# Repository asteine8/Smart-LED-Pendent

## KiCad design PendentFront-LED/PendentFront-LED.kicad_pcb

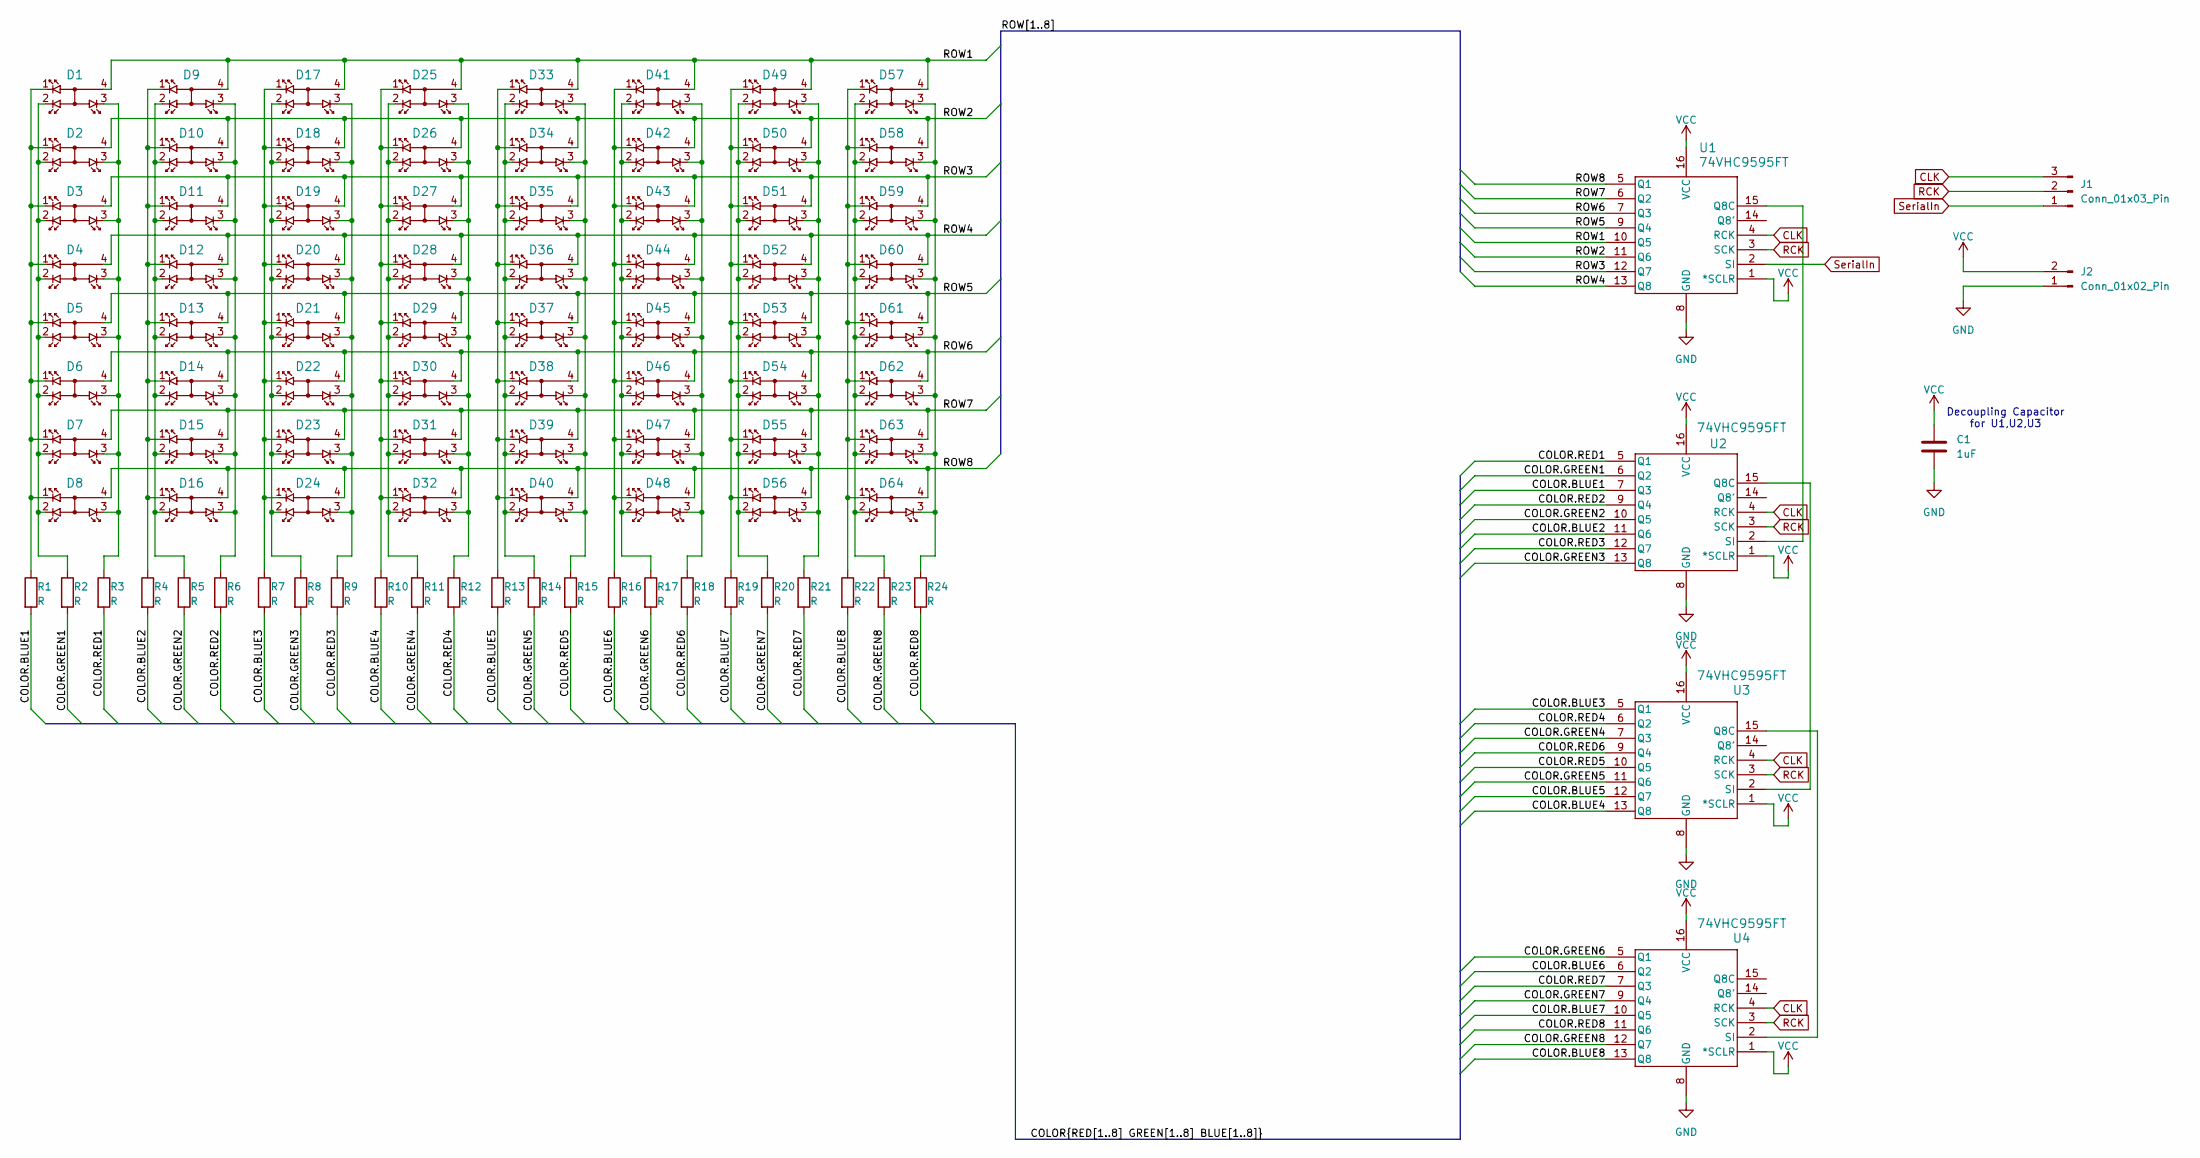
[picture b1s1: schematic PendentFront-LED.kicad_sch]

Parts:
C1: 1uF; C_0402_1005Metric_Pad0.74x0.62mm_HandSolder
D1, D2, D3, D4, D5, D6, D7, D8, D9, D10, D11, D12, D13, D14, D15, D16, D17, D18, D19, D20, D21, D22, D23, D24, D25, D26, D27, D28, D29, D30, D31, D32, D33, D34, D35, D36, D37, D38, D39, D40, D41, D42, D43, D44, D45, D46, D47, D48, D49, D50, D51, D52, D53, D54, D55, D56, D57, D58, D59, D60, D61, D62, D63, D64: UHD111A-FKA-C3K23E1L3VG5ZB3Z3; SMD4_UHD111A-FKA_CRW
J1: Conn_01x03_Pin; PinHeader_1x03_P1.27mm_Vertical
J2: Conn_01x02_Pin; PinHeader_1x02_P1.27mm_Vertical
R1, R2, R3, R4, R5, R6, R7, R8, R9, R10, R11, R12, R13, R14, R15, R16, R17, R18, R19, R20, R21, R22, R23, R24: R; R_0402_1005Metric
U1, U2, U3, U4: 74VHC9595FT; TSSOP16B_TOS

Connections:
/COLOR.BLUE1: R1.2, U2.7 (Q3)
/COLOR.BLUE2: R4.2, U2.11 (Q6)
/COLOR.BLUE3: R7.2, U3.5 (Q1)
/COLOR.BLUE4: R10.2, U3.13 (Q8)
/COLOR.BLUE5: R13.2, U3.12 (Q7)
/COLOR.BLUE6: R16.2, U4.6 (Q2)
/COLOR.BLUE7: R19.2, U4.10 (Q5)
/COLOR.BLUE8: R22.2, U4.13 (Q8)
/COLOR.GREEN1: R2.2, U2.6 (Q2)
/COLOR.GREEN2: R5.2, U2.10 (Q5)
/COLOR.GREEN3: R8.2, U2.13 (Q8)
/COLOR.GREEN4: R11.2, U3.7 (Q3)
/COLOR.GREEN5: R14.2, U3.11 (Q6)
/COLOR.GREEN6: R17.2, U4.5 (Q1)
/COLOR.GREEN7: R20.2, U4.9 (Q4)
/COLOR.GREEN8: R23.2, U4.12 (Q7)
/COLOR.RED1: R3.2, U2.5 (Q1)
/COLOR.RED2: R6.2, U2.9 (Q4)
/COLOR.RED3: R9.2, U2.12 (Q7)
/COLOR.RED4: R12.2, U3.6 (Q2)
/COLOR.RED5: R15.2, U3.10 (Q5)
/COLOR.RED6: R18.2, U3.9 (Q4)
/COLOR.RED7: R21.2, U4.7 (Q3)
/COLOR.RED8: R24.2, U4.11 (Q6)
/ROW1: D1.4, D9.4, D17.4, D25.4, D33.4, D41.4, D49.4, D57.4, U1.10 (Q5)
/ROW2: D2.4, D10.4, D18.4, D26.4, D34.4, D42.4, D50.4, D58.4, U1.11 (Q6)
/ROW3: D3.4, D11.4, D19.4, D27.4, D35.4, D43.4, D51.4, D59.4, U1.12 (Q7)
/ROW4: D4.4, D12.4, D20.4, D28.4, D36.4, D44.4, D52.4, D60.4, U1.13 (Q8)
/ROW5: D5.4, D13.4, D21.4, D29.4, D37.4, D45.4, D53.4, D61.4, U1.9 (Q4)
/ROW6: D6.4, D14.4, D22.4, D30.4, D38.4, D46.4, D54.4, D62.4, U1.7 (Q3)
/ROW7: D7.4, D15.4, D23.4, D31.4, D39.4, D47.4, D55.4, D63.4, U1.6 (Q2)
/ROW8: D8.4, D16.4, D24.4, D32.4, D40.4, D48.4, D56.4, D64.4, U1.5 (Q1)
CLK: J1.3, U1.4 (RCK), U2.4 (RCK), U3.4 (RCK), U4.4 (RCK)
GND: C1.2, J2.1, U1.8 (GND), U2.8 (GND), U3.8 (GND), U4.8 (GND)
unnamed: D1.1, D2.1, D3.1, D4.1, D5.1, D6.1, D7.1, D8.1, R1.1
unnamed: D1.2, D2.2, D3.2, D4.2, D5.2, D6.2, D7.2, D8.2, R2.1
unnamed: D1.3, D2.3, D3.3, D4.3, D5.3, D6.3, D7.3, D8.3, R3.1
unnamed: D9.1, D10.1, D11.1, D12.1, D13.1, D14.1, D15.1, D16.1, R4.1
unnamed: D9.2, D10.2, D11.2, D12.2, D13.2, D14.2, D15.2, D16.2, R5.1
unnamed: D9.3, D10.3, D11.3, D12.3, D13.3, D14.3, D15.3, D16.3, R6.1
unnamed: D17.1, D18.1, D19.1, D20.1, D21.1, D22.1, D23.1, D24.1, R7.1
unnamed: D17.2, D18.2, D19.2, D20.2, D21.2, D22.2, D23.2, D24.2, R8.1
unnamed: D17.3, D18.3, D19.3, D20.3, D21.3, D22.3, D23.3, D24.3, R9.1
unnamed: D25.1, D26.1, D27.1, D28.1, D29.1, D30.1, D31.1, D32.1, R10.1
unnamed: D25.2, D26.2, D27.2, D28.2, D29.2, D30.2, D31.2, D32.2, R11.1
unnamed: D25.3, D26.3, D27.3, D28.3, D29.3, D30.3, D31.3, D32.3, R12.1
unnamed: D33.1, D34.1, D35.1, D36.1, D37.1, D38.1, D39.1, D40.1, R13.1
unnamed: D33.2, D34.2, D35.2, D36.2, D37.2, D38.2, D39.2, D40.2, R14.1
unnamed: D33.3, D34.3, D35.3, D36.3, D37.3, D38.3, D39.3, D40.3, R15.1
unnamed: D41.1, D42.1, D43.1, D44.1, D45.1, D46.1, D47.1, D48.1, R16.1
unnamed: D41.2, D42.2, D43.2, D44.2, D45.2, D46.2, D47.2, D48.2, R17.1
unnamed: D41.3, D42.3, D43.3, D44.3, D45.3, D46.3, D47.3, D48.3, R18.1
unnamed: D49.1, D50.1, D51.1, D52.1, D53.1, D54.1, D55.1, D56.1, R19.1
unnamed: D49.2, D50.2, D51.2, D52.2, D53.2, D54.2, D55.2, D56.2, R20.1
unnamed: D49.3, D50.3, D51.3, D52.3, D53.3, D54.3, D55.3, D56.3, R21.1
unnamed: D57.1, D58.1, D59.1, D60.1, D61.1, D62.1, D63.1, D64.1, R22.1
unnamed: D57.2, D58.2, D59.2, D60.2, D61.2, D62.2, D63.2, D64.2, R23.1
unnamed: D57.3, D58.3, D59.3, D60.3, D61.3, D62.3, D63.3, D64.3, R24.1
unnamed: U1.15 (Q8C), U2.2 (SI)
unnamed: U2.15 (Q8C), U3.2 (SI)
unnamed: U3.15 (Q8C), U4.2 (SI)
RCK: J1.2, U1.3 (SCK), U2.3 (SCK), U3.3 (SCK), U4.3 (SCK)
SerialIn: J1.1, U1.2 (SI)
VCC: C1.1, J2.2, U1.1 (*SCLR), U1.16 (VCC), U2.1 (*SCLR), U2.16 (VCC), U3.1 (*SCLR), U3.16 (VCC), U4.1 (*SCLR), U4.16 (VCC)

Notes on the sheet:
Decoupling Capacitor for U1,U2,U3

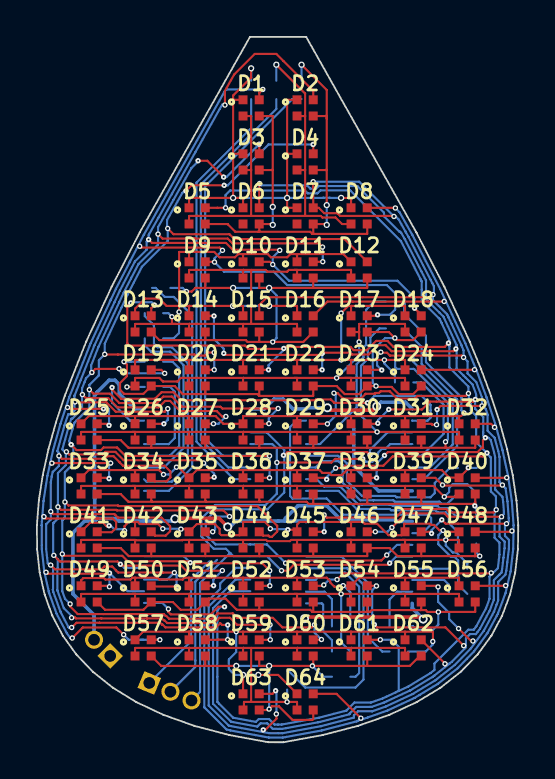
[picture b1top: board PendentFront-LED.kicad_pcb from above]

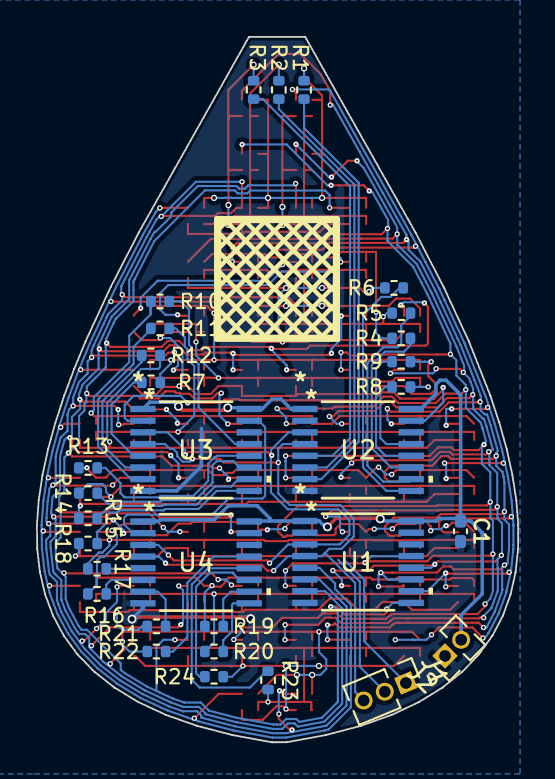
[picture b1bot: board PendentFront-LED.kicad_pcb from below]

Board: 2 copper layers, 26.7 x 39.2 mm, 95 parts (31 on the bottom side), 64 nets.

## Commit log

2025-09-10 Added board outline to pcb
    I need to manage my expectations
2025-09-10 removed lock
2025-09-13 Added Shape Outlines
2025-09-15 Finalized pendent shape and started routing
2025-09-19 Connected up shift registers. Still need to rearrange connections to make routing possible
2025-09-21 More work on routing the front LED panel
    Got through 2 1/2 groups of LEDs and reconfigured connections to shift registers to make routing easier. Split header into 2 groups for easier placement
2025-09-21 routing
2025-10-04 More routing
2025-10-05 More routing, started putting row lines around the outside of the pendent
2025-10-07 Nearly done with routing
2025-10-31 Tried to get CTRL inputs to get connected - needs some squeezing
